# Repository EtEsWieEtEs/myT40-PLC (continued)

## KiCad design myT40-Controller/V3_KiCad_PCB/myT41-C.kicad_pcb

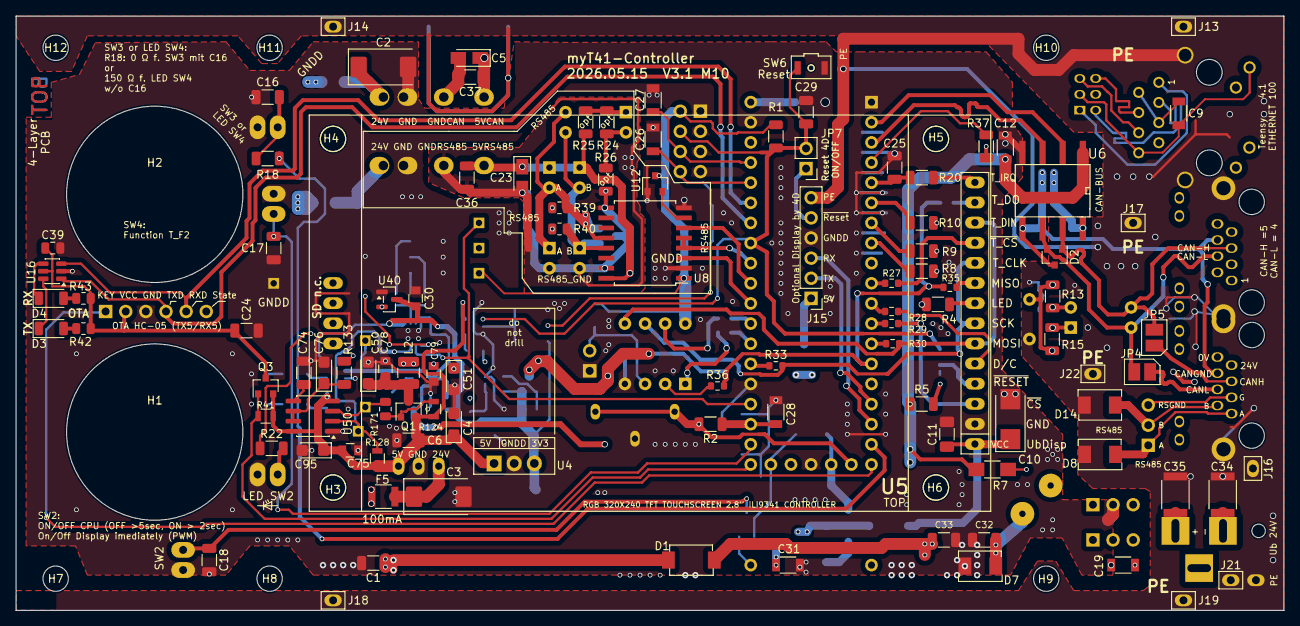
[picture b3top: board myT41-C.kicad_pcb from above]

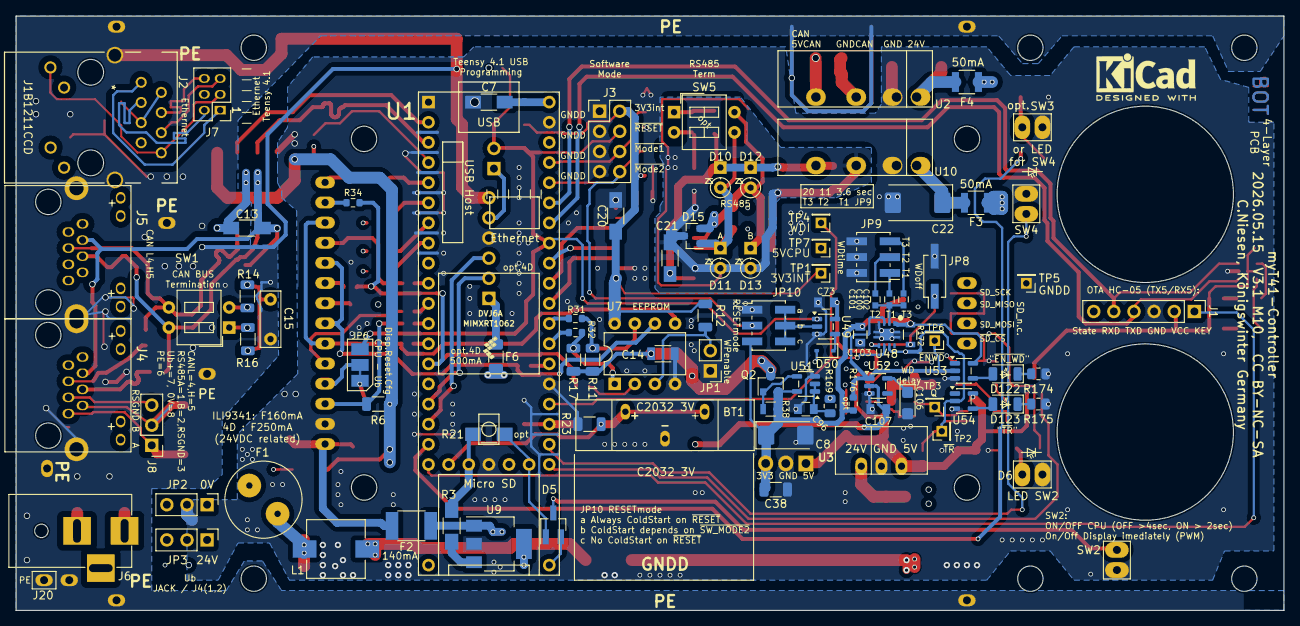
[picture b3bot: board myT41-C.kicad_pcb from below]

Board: 4 copper layers, 160.0 x 75.0 mm, 209 parts (94 on the bottom side), 132 nets.

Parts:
A1: mySymbol; KiCad-Logo2_6mm_SilkScreen
BT1: 3V Lithium 2032; BAT_2032
C1, C6, C16, C17, C18, C24, C25, C29, C36, C37, C38: KEM X7R, 100n 50V; C_1206_3216Metric
C2, C3, C22: T491D Tantal, 10µF, 50V; CP_EIA-7343-31_Kemet-D
C4: TAJ 3516 22/10; CP_EIA-3216-18_Kemet-A
C5, C23: TAJ 3516 22/10; CP_Tantalum_Case-A_EIA-3216-18_Reflow
C7, C13, C20, C21: KEM X7R, 100n 50V; C_1206_HandSoldering
C8: T495D 100µF, 10V; CP_EIA-6032-28_Kemet-C
C9: KEM X7R 100n 50V; C_1206
C10: T495D 22µF 10V; CP_Tantalum_Case-C_EIA-6032-28_Reflow
C11: KEM X7R 100n 50V; C_1206_3216Metric_Pad1.33x1.80mm_HandSolder
C12, C14, C26, C27, C28, C31: KEM X7R, 100n 50V; C_1206
C15: 4n7; C_Rect_L7.0mm_W2.5mm_P5.00mm
C19: KEM X7R, 100n 100V; C_1206
C30, C73, C75, C96, C103, C107: 100n; C_0805
C32, C33: 100n 100V; C_1206_3216Metric
C34, C35: 2n2 Y3; C_1812
C39: KEM X7R 100n 50V; C_0805_2012Metric
C50, C51: 4µ7 16V; CP_EIA-3216-18_Kemet-A
C74: 10n; C_1206_3216Metric
C76, C95: 10µ 10V; CP_EIA-3216-18_Kemet-A
C78, C79: 2,2pF; C_0805
C100: 47n; C_0603
C101: 150n; C_0603
C102: 270n; C_0603
C106: 3µ3 10V; CP_EIA-3216-18_Kemet-A
D1: MBRS 1100 SMD; DO-214AA_Schottky_man
D2, D15: SZNUP2105LT1G; SOT-23
D3, D4, D122, D123: APTD3216; LED_1206_3216_big-gap
D5: BAT54C; SOT-23_Handsoldering
D6: LED_SW2; Lötauge-Junction-Dual-3x2
D7: SM6T 30CA STM; DO-214AA
D8, D14: P6SMB 5,0CA; DO-214AA
D10, D11, D12, D13: BAT46; D_DO-35_SOD27_P2.54mm_Vertical_KathodeUp
D50: RB751V40T1G; D_SOD-323
F1: 160mA F; Sockel_Kleinst-F
F2: Ih=140mA (PTC FSMD014R); R_1812
F3, F4: Ih=50mA; R_1210
F5: Ih=100mA; R_1210
F6: Ih=500mA (PTS12066V050); C_1206_3216Metric_Pad1.33x1.80mm_HandSolder
H1, H2, H3, H4, H5: MountingHole; MountingHole_3mm
H6, H7, H8, H9, H10, H11, H12: MountingHole; MountingHole_3.2mm_M3_DIN965
J1: Connector OTA HC-05; PinHeader_1x06_P2.54mm_Vertical
J2: J1B1211CCD; RJ45_J1B1211CCD
J3: 02x04-OE; PinHeader_2x04_P2.54mm_Vertical
J4, J5: 8P8C_LED_Shielded; RJ45-LED
J6: Barrel-Jack; BARREL_JACK_5.5_2.1
J7: <<-- Kabel; PinHeader_2x03_P2.00mm_Vertical
J8: drilled wire; PinHeader_1x03_P2.54mm_Vertical
J13, J14, J17, J18, J19: Conn_01x01; Lötauge-Junction
J15: Connector 4D gen4; PinHeader_1x06_P2.54mm_Vertical
J16, J20, J21, J22: Lötpunkt; Lötauge-Junction
JP1: WriteProtection; PinHeader_1x02_P2.54mm_Vertical
JP2: 0V CAN / JACK; PinHeader_1x03_P2.54mm_Vertical
JP3: 24V J4/JACK; PinHeader_1x03_P2.54mm_Vertical
JP4: CAN-L; Solder-Junction-2,2x1,5
JP5: CAN-H; Solder-Junction-2,2x1,5
JP6: DisplayResetConfig; Solder-Junction-3x2.2x1.5_1-2-closed
JP7: Reset enable; PinHeader_1x02_P2.54mm_Vertical
JP8: Jumper_NC_Small; PinHeader_2x01_P2.54mm_Vertical_SMD
JP9: Watchdog Time; PinHeader_2x03_P2.00mm_Vertical_SMD
JP10: Restart Mode on ~{RESET}; PinHeader_2x03_P2.00mm_Vertical_SMD
L1: 270µH; L_7.3x7.3_H3.5_handsoldered
L2: 47µH; L_1210_3225Metric
Q1, Q2, Q3: IRLML 2244; SOT-23
R1, R5, R6, R11, R12, R17: 3K3; R_1206_3216Metric
R2, R23: 680k; R_1206_3216Metric
R3: 270; R_1206_HandSoldering
R4: 470; R_1206_3216Metric
R7: 150; R_1206_HandSoldering
R8, R9, R10, R18, R22, R37: 150; R_1206_3216Metric
R13, R14, R15, R16, R24: 120; R_1206_3216Metric
R20: 10K; R_1206_3216Metric
R21: (3K3 opt); R_1206_HandSoldering
R25, R26: 730; R_1206_3216Metric
R27, R28, R29, R30, R31, R32, R33, R34, R35, R36: 51; R_0603_1608Metric
R38, R41, R124: 10k; R_0805
R39, R40, R169, R171: 10; R_0805_2012Metric
R42, R43: 3K3; R_0805_2012Metric
R128: 47k; R_0805
R133: 220k; R_1206_3216Metric
R172: 1k; R_1206_vertical
R174: 1650; R_0805_2012Metric
R175: 3k3; R_0805_2012Metric
R176: 10k; R_0603_1608Metric
SW1, SW5: SW_DIP_x02; SW_DIP_x2_W7.62mm_Slide_LowProfile
SW2: On/Off; Lötauge-Junction-Dual-3x2
SW3: F1; Lötauge-Junction-Dual-3x2
SW4: F2; Lötauge-Junction-Dual-3x2
SW6: Reset; switch-tactil_OMRON_B3U-3000P
TP1: 3V3int; PinHeader_1x01_P2.00mm_Vertical
TP2: TR; PinHeader_1x01_P2.00mm_Vertical
TP3: Q; PinHeader_1x01_P2.00mm_Vertical
TP4: WDI; PinHeader_1x01_P2.00mm_Vertical
TP5: GNDD; PinHeader_1x01_P2.00mm_Vertical
TP6: EN_WD; PinHeader_1x01_P2.00mm_Vertical
TP7: 5V_CPU; PinHeader_1x01_P2.00mm_Vertical
U1: Teensy4.1; Teensy41_mod
U2, U10: 2S7WA_2405_S3RP; SIP-7_2S7WA
U3: LC78_05-1.0; SIP-3-LC78
U4: LM 3940 IT3,3; TO-220-3_Vertical
U5: ili9341_touch; ILI9341
U6: ISO1050DUB; SOP-8
U7: 25LC512-I/P; DIP-8_W7.62mm
U8: ADM2483xRW; SOIC-16W_7.5x10.3mm_Pitch1.27mm_handsoldered
U9: BSP-452; SOT-223
U12: ADM-809Z; SOT-23
U16: 74LVC2G07; SOT-23-6
U40: ADM-803S; SOT-23
U48: TPS3431; VSON-8_EP_2.8x2.8_Pitch0.65mm
U49: SN74LV1T32; SOT-23-5
U50: NE555DRG4; SOIC-8_3.9x4.9mm_P1.27mm
U51: SN74LV1T08; SOT-23-5
U52: S-80929CNMC; SOT-23-5
U53, U54: BD7LS04G-C; SOT-23-5

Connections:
3V3_INT: C12.1, C14.2, C20.1, C107.1, J3.2, Q2.3 (D), R1.1, R5.1, R6.1, R7.1, R11.1, R12.1, R17.1, TP1.1, U6.1 (VCC1), U7.8 (VCC), U8.1 (VDD1), U12.3 (VCC), U52.2 (VDD)
5V_CPU: C7.1, C51.1, C79.1, L2.2, TP7.1, U1.48 (VIN)
+3V3: C8.1, C30.2, C38.1, C103.2, JP10.5, Q2.2 (S), R38.2, R172.1, R176.1, U4.3 (VO), U40.3 (VCC), U48.1 (VDD), U51.5 (VCC), U53.5 (VCC)
+5V: C4.1, C6.1, C31.1, C73.2, C75.2, C95.1, Q1.2 (S), Q3.2 (S), R41.1, R124.1, R128.2, R133.2, U3.3 (VO), U4.1 (VI), U9.4 (VCC), U49.5 (VCC), U50.4 (R), U50.8 (VCC), U54.5 (VCC)
+24V: C1.1, D1.1 (K), F3.1, F4.1, F5.1
/UpperPCB/BAT_CHECK: C28.1, R2.1, U1.32 (40_A16)
/UpperPCB/CAN1H: D2.1 (A1), J5.5, JP5.2 (B), SW1.3, U6.7 (CANH)
/UpperPCB/CAN1L: D2.2 (A2), J5.4, JP4.2 (B), SW1.4, U6.6 (CANL)
/UpperPCB/CANRX: U1.2 (0_RX1_CRX2_CS1), U6.2 (RXD)
/UpperPCB/CANTX: U1.3 (1_TX1_CTX2_MISO1), U6.3 (TXD)
/UpperPCB/DC: R28.2, U5.5 (D/C)
/UpperPCB/D_LED_PWM: R4.1, U1.9 (7_RX2_OUT1A)
/UpperPCB/D_SLEEP: D5.2, U1.25 (33_MCLK2)
/UpperPCB/D_VCC_ON: R3.1, R21.1, U1.51 (3V3)
/UpperPCB/E24V: C19.1, F1.2, JP3.2
/UpperPCB/ETH_GND: C9.1, J2.8, J2.9, J7.3
/UpperPCB/ETH_LED: J2.10, J7.4
/UpperPCB/ETH_R+: J2.4, J7.6
/UpperPCB/ETH_R-: J2.6, J7.5
/UpperPCB/ETH_T+: J2.1, J7.1
/UpperPCB/ETH_T-: J2.3, J7.2
/UpperPCB/GND_CAN_BUS: C5.2, C13.2, C37.2, D2.3 (common), J4.6, J5.6, U2.4 (Out-), U6.5 (GND2)
/UpperPCB/LED1: R10.1, U1.6 (4_BCLK2)
/UpperPCB/LED2: R9.1, U1.7 (5_IN2)
/UpperPCB/LED3: R8.1, U1.8 (6_OUT1D)
/UpperPCB/LED4: R37.1, U1.4 (2_OUT2)
/UpperPCB/MISO: R34.2, R35.1, R36.1, U1.14 (12_MISO_MQSL)
/UpperPCB/MOSI: R30.2, U5.6 (SDI_MOSI), U5.12 (T_DIN), U7.5 (MOSI)
/UpperPCB/ON-OFF: D5.1, R21.2, U1.54 (ON_OFF)
/UpperPCB/OTA_KEY: J1.1, U1.19 (27_A13_SCK1)
/UpperPCB/OTA_RX: J1.5, U1.43 (21_A7_RX5_BCLK1), U16.3
/UpperPCB/OTA_TX: J1.4, U1.42 (20_A6_TX5_LRCLK1), U16.1
/UpperPCB/RS485+: D8.2 (A2), J4.1, J8.1, R39.2
/UpperPCB/RS485-: D14.1 (A1), J4.2, J8.2, R40.2
/UpperPCB/RS485-A: D12.2 (A), D13.1 (K), D15.2 (A2), R39.1, SW5.4, U8.12 (A)
/UpperPCB/RS485-B: D10.2 (A), D11.1 (K), D15.1 (A1), R40.1, SW5.3, U8.13 (B)
/UpperPCB/RS485_GND: C21.2, C23.2, C36.2, D11.2 (A), D13.2 (A), D15.3 (common), J4.3, J8.3, R26.1, U8.9 (GND2), U8.15 (GND2), U10.4 (Out-)
/UpperPCB/RX_4D: J15.3, U1.17 (25_A11_RX6_SDA2)
/UpperPCB/SPISCK: R33.1, U5.7 (SCK), U5.10 (T_CLK), U7.6 (SCK)
/UpperPCB/TX_4D: J15.2, U1.16 (24_A10_TX6_SCL2)
/UpperPCB/T_F1: R18.1, U1.18 (26_A12_MOSI1)
/UpperPCB/T_F2: C17.1, SW4.1, U1.31 (39_MISO1_OUT1A)
/UpperPCB/T_IRQ: C25.1, R20.2, U1.5 (3_LRCLK2)
/UpperPCB/UART_RX: U1.38 (16_A2_RX4_SCL1), U8.3 (RxD)
/UpperPCB/UART_TX: U1.39 (17_A3_TX4_SDA1), U8.6 (TxD)
/UpperPCB/UbDisplay: C10.1, C11.1, F2.2, U5.1 (VCC)
/UpperPCB/Ub_CAN_BUS: C5.1, C13.1, C37.1, U2.6 (Out+), U6.8 (VCC2)
/UpperPCB/Ub_RS485: C21.1, C23.1, C36.1, D10.1 (K), D12.1 (K), R25.2, U8.16 (VDD2), U10.6 (Out+)
/UpperPCB/VBAT: BT1.1 (+), R2.2, R23.2, U1.50 (VBAT)
/UpperPCB/~CS_D: R6.2, R29.2, U5.3 (~CS)
/UpperPCB/~CS_T: R27.2, U5.11 (~T_CS)
/UpperPCB/~EE_CS: R17.2, R32.1, U7.1 (~CS)
/UpperPCB/~EE_HOLD: R11.2, R31.1, U7.7 (~HOLD)
/UpperPCB/~SW_MODE_1: C27.1, J3.6, U1.45 (23_A9_CRX1_MCLK1)
/UpperPCB/~UART_RE: U1.40 (18_A4_SDA), U8.4 (~RE), U8.5 (DE)
/UpperPCB/~WP: JP1.2 (B), R12.2, U7.3 (~WP)
/WatchdogMod/EN_WD: R176.2, TP6.1, U48.3 (EN), U52.1 (OUT), U53.2
/WatchdogMod/TR-U50: D50.2 (A), R128.1, TP2.1, U40.2 (~RESET), U48.7 (~WDO), U50.2 (TR), U54.2
Earth: C15.2, C34.1, C35.2, D8.1 (A1), D14.2 (A2), J2.SH, J4.SH, J5.SH, J13.1, J14.1, J15.6, J16.1, J17.1, J18.1, J19.1, J20.1, J21.1, J22.1
GNDD: BT1.2 (-), C1.2, C2.2, C3.2, C4.2, C6.2, C7.2, C8.2, C10.2, C11.2, C12.2, C14.1, C16.2, C17.2, C18.2, C19.2, C20.2, C22.2, C24.2, C25.2, C26.2, C27.2, C28.2, C29.2, C30.1, C31.2, C32.2, C33.2, C38.2, C39.1, C50.2, C51.2, C73.1, C74.1, C75.1, C76.2, C78.2, C79.2, C95.2, C96.2, C103.1, C106.2, C107.2, D6.1 (K), D7.1 (A1), J1.3, J2.11, J3.1, J3.3, J3.5, J3.7, J4.9, J4.11, J5.9, J5.11, J15.4, JP1.1 (A), JP2.2, JP8.2, JP9.2, JP9.4, JP9.6, JP10.1, R23.1, R174.1, R175.1, SW2.2, SW3.2, SW4.2, SW6.1, TP5.1, U1.1 (GND), U1.34 (GND), U1.47 (GND), U1.52 (GND), U2.2 (In-), U3.2 (GND), U4.2 (GND), U5.2 (GND), U6.4 (GND1), U7.4 (GND), U8.2 (GND1), U8.8 (GND1), U9.2 (GND), U10.2 (In-), U12.1 (GND), U16.2 (GND), U40.1 (GND), U48.4 (GND), U48.9 (Pad), U49.3 (GND), U50.1 (GND), U51.3 (GND), U52.3 (VSS), U53.3 (GND), U54.3 (GND)
unnamed: C9.2, J2.2, J2.5
unnamed: C15.1, R13.1, R14.1, R15.1, R16.1
unnamed: C16.1, R18.2, SW3.1
unnamed: C18.1, D5.3, SW2.1
unnamed: C34.2, J6.2, JP2.3
unnamed: C35.1, J6.1, JP3.3
unnamed: C96.1, R169.2, U51.1, U51.2
unnamed: C33.1, D1.2 (A), L1.1
unnamed: D3.2 (A), R42.2
unnamed: D3.1 (K), U16.6
unnamed: D4.2 (A), R43.2
unnamed: D4.1 (K), U16.4
unnamed: D6.2 (A), R22.2
unnamed: C32.1, D7.2 (A2), F1.1, L1.2
unnamed: D50.1 (K), U49.4
unnamed: D122.2 (A), U53.4
unnamed: D122.1 (K), R174.2
unnamed: D123.2 (A), U54.4
unnamed: D123.1 (K), R175.2
unnamed: J2.12, R37.2
unnamed: J4.7, JP3.1
unnamed: J4.8, JP2.1
unnamed: J4.10, R7.2
unnamed: J4.12, R8.2
unnamed: J5.10, R9.2
unnamed: J5.12, R10.2
unnamed: F6.1, J15.1
unnamed: J15.5, JP7.1
unnamed: J4.4, JP4.1 (A)
unnamed: J4.5, JP5.1 (A)
unnamed: JP6.1 (A), R5.2
unnamed: JP6.2 (C), U5.4 (~RESET)
unnamed: C100.2, JP9.1
unnamed: C101.1, JP9.3
unnamed: C102.1, JP9.5
unnamed: JP10.2, JP10.4, JP10.6, U49.2
unnamed: C50.1, C78.1, L2.1, Q1.3 (D)
unnamed: Q1.1 (G), R124.2, R171.2
unnamed: Q2.1 (G), R38.1, U51.4
unnamed: R13.2, R14.2, SW1.2
unnamed: R15.2, R16.2, SW1.1
unnamed: R24.1, R25.1, SW5.1
unnamed: R24.2, R26.2, SW5.2
unnamed: R27.1, U1.10 (8_TX2_IN1)
unnamed: R28.1, U1.11 (9_OUT1C)
unnamed: R29.1, U1.12 (10_CS_MQSR)
unnamed: R30.1, U1.13 (11_MOSI_CTX1)
unnamed: R33.2, U1.35 (13_SCK_LED)
unnamed: R32.2, U1.36 (14_A0_TX3_SPDIF_OUT)
unnamed: R31.2, U1.37 (15_A1_RX3_SPDIF_IN)
unnamed: C2.1, F4.2, U2.1 (In+)
unnamed: C3.1, F5.2, U3.1 (VI)
unnamed: R4.2, U5.8 (LED)
unnamed: R35.2, U5.9 (SDO_MISO)
unnamed: R34.1, U5.13 (T_DO)
unnamed: R20.1, U5.14 (T_IRQ)
unnamed: R36.2, U7.2 (MISO)
unnamed: R3.2, U9.3 (IN)
unnamed: F2.1, F6.2, U9.1 (OUT)
unnamed: C22.1, F3.2, U10.1 (In+)
unnamed: U8.7 (PV), U12.2 (~RESET)
unnamed: C100.1, C101.2, C102.2, U48.2 (CWD)
unnamed: JP8.1, R172.2, U48.5 (SET1)
unnamed: C74.2, U50.5 (CV)
unnamed: C76.1, R133.1, U50.6 (THR), U50.7 (DIS)
unnamed: C106.1, U52.5 (CD)
OTA_5V: C24.1, C39.2, J1.2, Q3.3 (D), R42.1, R43.1, U16.5 (VCC)
OTA_EN: Q3.1 (G), R41.2, U1.30 (38_CS1_IN1)
WDI: R22.1, TP4.1, U1.33 (41_A17), U48.6 (WDI)
~Q: R169.1, R171.1, TP3.1, U50.3 (Q)
~RESET: C29.1, J3.4, JP6.3 (B), JP7.2, R1.2, SW6.2, U1.41 (19_A5_SCL), U49.1
~SW_MODE_2: C26.1, J3.8, JP10.3, U1.44 (22_A8_CTX1)

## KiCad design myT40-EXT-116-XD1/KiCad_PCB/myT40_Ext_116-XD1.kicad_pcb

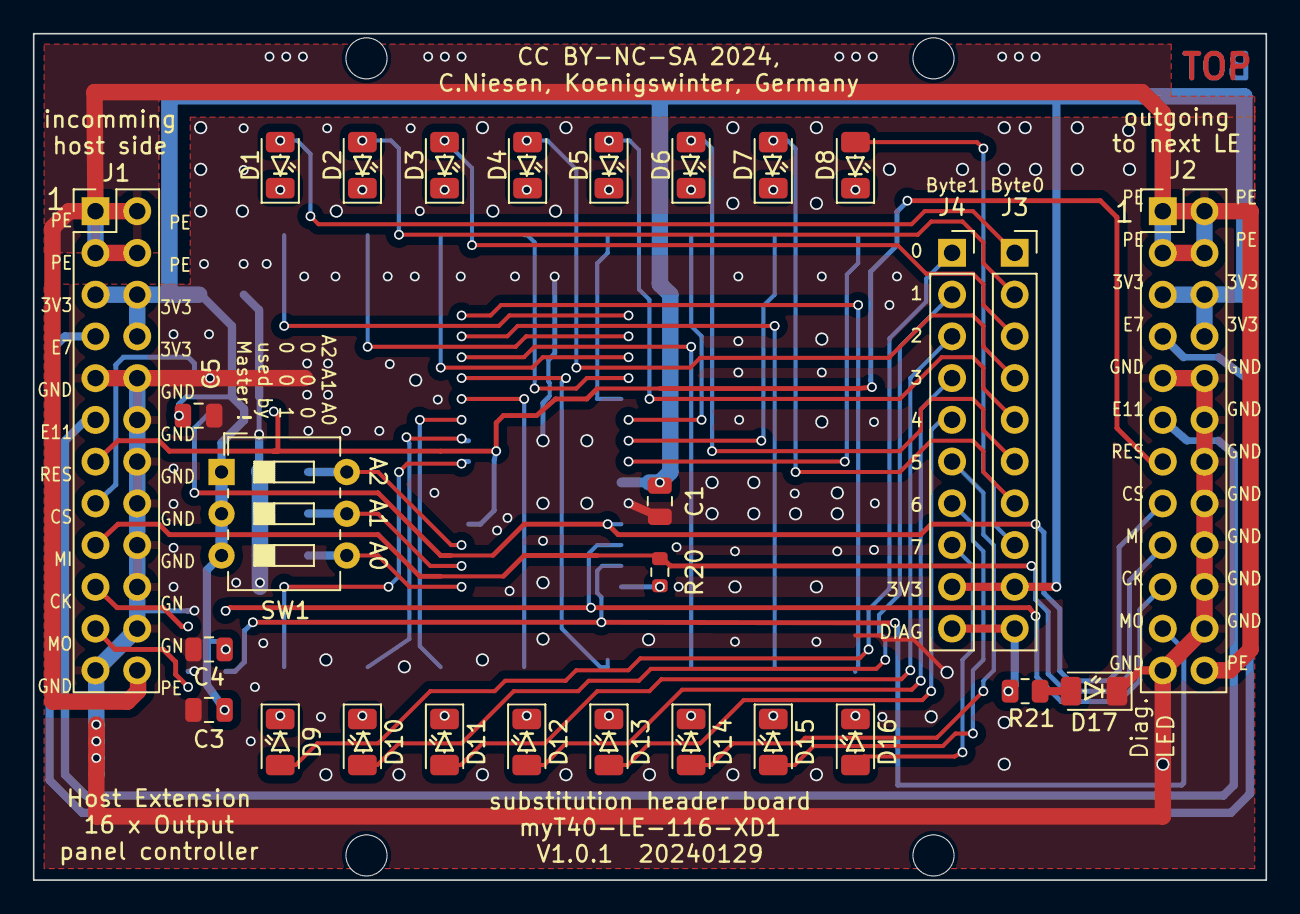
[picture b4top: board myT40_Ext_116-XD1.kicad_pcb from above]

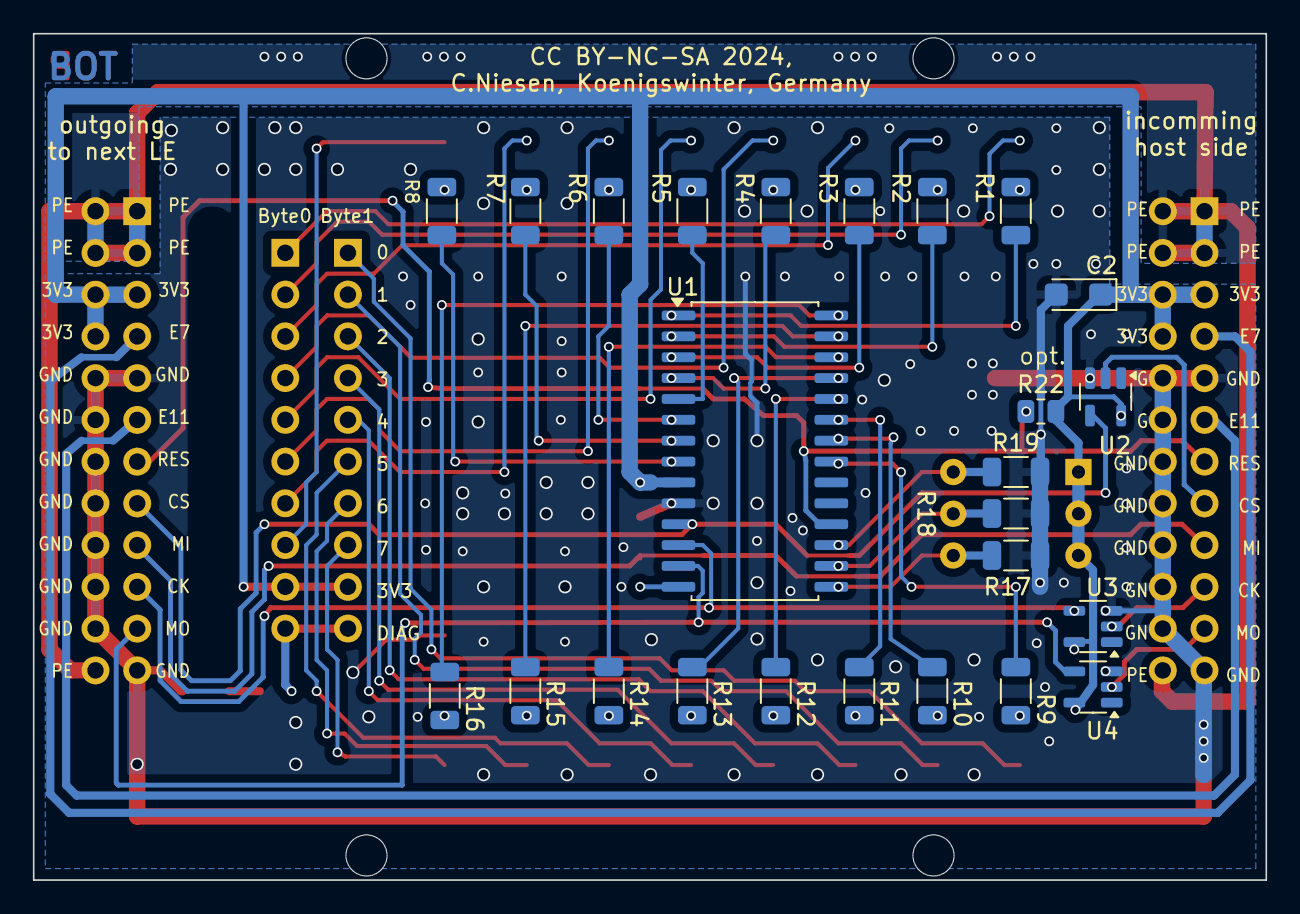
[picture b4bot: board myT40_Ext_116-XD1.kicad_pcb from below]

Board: 2 copper layers, 75.0 x 51.5 mm, 58 parts (25 on the bottom side), 67 nets.

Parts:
C1, C3, C4, C5: 100n; C_0805_2012Metric
C2: 1µ5; CP_EIA-3216-18_Kemet-A
D1, D2, D3, D4, D5, D6, D7, D8, D9, D10, D11, D12, D13, D14, D15, D16, D17: KPTD-3216; LED_1206_3216Metric
H1, H2, H3, H4, H5: MountingHole; MountingHole_2.5mm
J1: Ext-In 2x12; PinHeader_2x12_P2.54mm_Vertical
J2: Ext-Out 2x12; PinHeader_2x12_P2.54mm_Vertical
J3: Byte0 01x10; PinSocket_1x10_P2.54mm_Vertical
J4: Byte1 01x10; PinSocket_1x10_P2.54mm_Vertical
R1, R2, R3, R4, R5, R6, R7, R8, R9, R10, R11, R12, R13, R14, R15, R16: 270; R_1206_3216Metric
R17, R18, R19: 10k; R_1206_3216Metric
R20: 51; R_0603_1608Metric
R21: 470; R_0805_2012Metric
R22: 68k; R_0805_2012Metric
SW1: SW_DIP_x03; SW_DIP_SPSTx03_Slide_6.7x9.18mm_W7.62mm_P2.54mm_LowProfile
U1: MCP23S17_SO; SOIC-28W_7.5x17.9mm_P1.27mm
U2, U3, U4: SN74LVC1G17DBVTE4; SOT-23-5

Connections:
/3V3_INT: C1.1, C2.1, C3.1, C4.1, C5.1, J1.5, J1.6, J1.8, J2.5, J2.6, J2.8, J3.9, J4.9, R22.2, SW1.1, SW1.2, SW1.3, U1.9 (VDD), U2.5 (VCC), U3.5 (VCC), U4.5 (VCC)
/EXT_7: J1.7, J2.7
/EXT_11: J1.11, J2.11
/MISO: J1.17, J2.17, R20.2
/MOSI: J2.21, U1.13 (SI), U4.4
/MOSI_: J1.21, U4.2
/PE: J1.1, J1.2, J1.3, J1.4, J1.24, J2.1, J2.2, J2.3, J2.4, J2.24
/SPISCK: J2.19, U1.12 (SCK), U3.4
/SPISCK_: J1.19, U3.2
/~RESET: J1.13, J2.13, R22.1, U1.18 (~RESET)
/~SPICS_IO_: J1.15, U2.2
/~SPICS_IO: J2.15, U1.11 (~CS), U2.4
GNDD: C1.2, C2.2, C3.2, C4.2, C5.2, D17.1 (K), J1.9, J1.10, J1.12, J1.14, J1.16, J1.18, J1.20, J1.22, J1.23, J2.9, J2.10, J2.12, J2.14, J2.16, J2.18, J2.20, J2.22, J2.23, R17.1, R18.1, R19.1, U1.10 (VSS), U2.3 (GND), U3.3 (GND), U4.3 (GND)
unnamed: D1.2 (A), J3.1
unnamed: D1.1 (K), R1.2
unnamed: D2.2 (A), J3.2
unnamed: D2.1 (K), R2.2
unnamed: D3.2 (A), J3.3
unnamed: D3.1 (K), R3.2
unnamed: D4.2 (A), J3.4
unnamed: D4.1 (K), R4.2
unnamed: D5.2 (A), J3.5
unnamed: D5.1 (K), R5.2
unnamed: D6.2 (A), J3.6
unnamed: D6.1 (K), R6.2
unnamed: D7.2 (A), J3.7
unnamed: D7.1 (K), R7.2
unnamed: D8.2 (A), J3.8
unnamed: D8.1 (K), R8.2
unnamed: D9.2 (A), J4.1
unnamed: D9.1 (K), R9.2
unnamed: D10.2 (A), J4.2
unnamed: D10.1 (K), R10.2
unnamed: D11.2 (A), J4.3
unnamed: D11.1 (K), R11.2
unnamed: D12.2 (A), J4.4
unnamed: D12.1 (K), R12.2
unnamed: D13.2 (A), J4.5
unnamed: D13.1 (K), R13.2
unnamed: D14.2 (A), J4.6
unnamed: D14.1 (K), R14.2
unnamed: D15.2 (A), J4.7
unnamed: D15.1 (K), R15.2
unnamed: D16.2 (A), J4.8
unnamed: D16.1 (K), R16.2
unnamed: D17.2 (A), R21.1
unnamed: J3.10, J4.10, R21.2
unnamed: R17.2, SW1.4, U1.15 (A0)
unnamed: R18.2, SW1.5, U1.16 (A1)
unnamed: R19.2, SW1.6, U1.17 (A2)
unnamed: R9.1, U1.21 (GPA0)
unnamed: R10.1, U1.22 (GPA1)
unnamed: R11.1, U1.23 (GPA2)
unnamed: R12.1, U1.24 (GPA3)
unnamed: R13.1, U1.25 (GPA4)
unnamed: R14.1, U1.26 (GPA5)
unnamed: R15.1, U1.27 (GPA6)
unnamed: R16.1, U1.28 (GPA7)
unnamed: R1.1, U1.1 (GPB0)
unnamed: R2.1, U1.2 (GPB1)
unnamed: R3.1, U1.3 (GPB2)
unnamed: R4.1, U1.4 (GPB3)
unnamed: R5.1, U1.5 (GPB4)
unnamed: R6.1, U1.6 (GPB5)
unnamed: R7.1, U1.7 (GPB6)
unnamed: R8.1, U1.8 (GPB7)
unnamed: R20.1, U1.14 (SO)

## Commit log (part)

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2023-11-17 First Upload myT40-...
2023-11-17 Renaming filenames of pictures
2023-11-21 Errata Schaltplan
2023-11-25 Kaltstart-Erweiterung auf 3V3 mit Q2
2023-11-25 Dokumentation Readme, Ankündigung der Überarbeitung und M37
2023-11-26 Dokumentation V2.6 M36 redaktionell überarbeitet, M37 noch nicht enthalten
2023-12-04 V2.6 M37 PFS
2023-12-04 U49 Comment
2023-12-04 C75 Result
2023-12-04 SCH unreadable
2023-12-04 Create HT40_PFS_2.6_M37_SCH.pdf
    New SCH
2023-12-05 Edit Doc and PartsList
2023-12-06 Ansteuerung Q2 verändert
    Ansteuerung auf UP über Brücke J34 J36 ist entfallen.
2023-12-06 STKL angepasst
2023-12-15 OP routing optimized
2023-12-15 OP PCB mods CPU
2023-12-15 OP variant 4 Layer PCB
2023-12-15 Edit comment PCB
2023-12-15 PCB V2.6 M37 vom 15.12.2023
    see readme
2023-12-15 Edit readme
2023-12-22 Kaltstart Überarbeitung
2023-12-29 Überarbeitung 4-Layer-Layout und Dokumentation
2024-03-01 V2.6 R38 final PFS
    M38 final Version for PFS variant
2024-03-15 Updated documentation to M38 produced as V4
2024-05-27 V2.8 M40 Coldstart Issues
    Coldstart issues, some PullUps to high dimensioned, no high logic resulting together with switched-off Teensy and its input impedances.
2024-07-04 Update README.md
    continuing developement of Prototype4 /M38
2024-07-04 myT40-PLC_M38-modified-as-M40
2024-07-05 Final version V2.9 M41
    Cold start issues solved.
2024-07-06 M41 published
2024-07-31 Edit for M41 R2.9
    The final documentation for corrected M38 is now M41.
    Expected M42 with external HW-watchdog will follow later.
2024-07-31 M41 edit PLC readme
2024-07-31 Edit PLC readme
2025-11-20 V5 is ready
    V5 is ready.
    Doc in writing.
    New is: external watchdog plus delay for this watchdog.
2025-11-20 V5 Previews (variant PFS)
    V5 Previews (variant PFS)
2025-11-27 Version-5-Final Dokumentation Draft
    Dokumentation Draft Version-5-final (V3.1.M43) PFS
2026-05-17 Final V5 Upload
    Uploading final Version May 2026 V5
    PCB, Partslist, Sheets.
    Doku outstanding
2026-05-17 Update PLC Main Readme
2026-05-17 myT41-Controller V3.1
2026-05-18 Docu and extention
2026-05-18 Project Readme
2026-05-18 translation hint
2026-05-18 liste
2026-05-18 liste2
2026-05-18 liste3
2026-05-18 Liste4
2026-05-18 pic subtext
2026-05-18 pdf optimierung
2026-05-18 Prototype-1
